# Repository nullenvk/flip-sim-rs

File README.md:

# FLIP

FLIP simulation made in rust. Based on work of Matthias Müller

https://github.com/matthias-research

https://matthias-research.github.io/pages/tenMinutePhysics/index.html

UWAGA: Program należy kompilować z flagą `--release`, w przeciwnym wypadku simulation loop jest dosyć powolny (pełne 60 FPS w release mode vs około 3 FPS w debug mode).

Jak uruchomić:
`cargo run --release`

Parametry symulacji można edytować w `src/main.rs`.

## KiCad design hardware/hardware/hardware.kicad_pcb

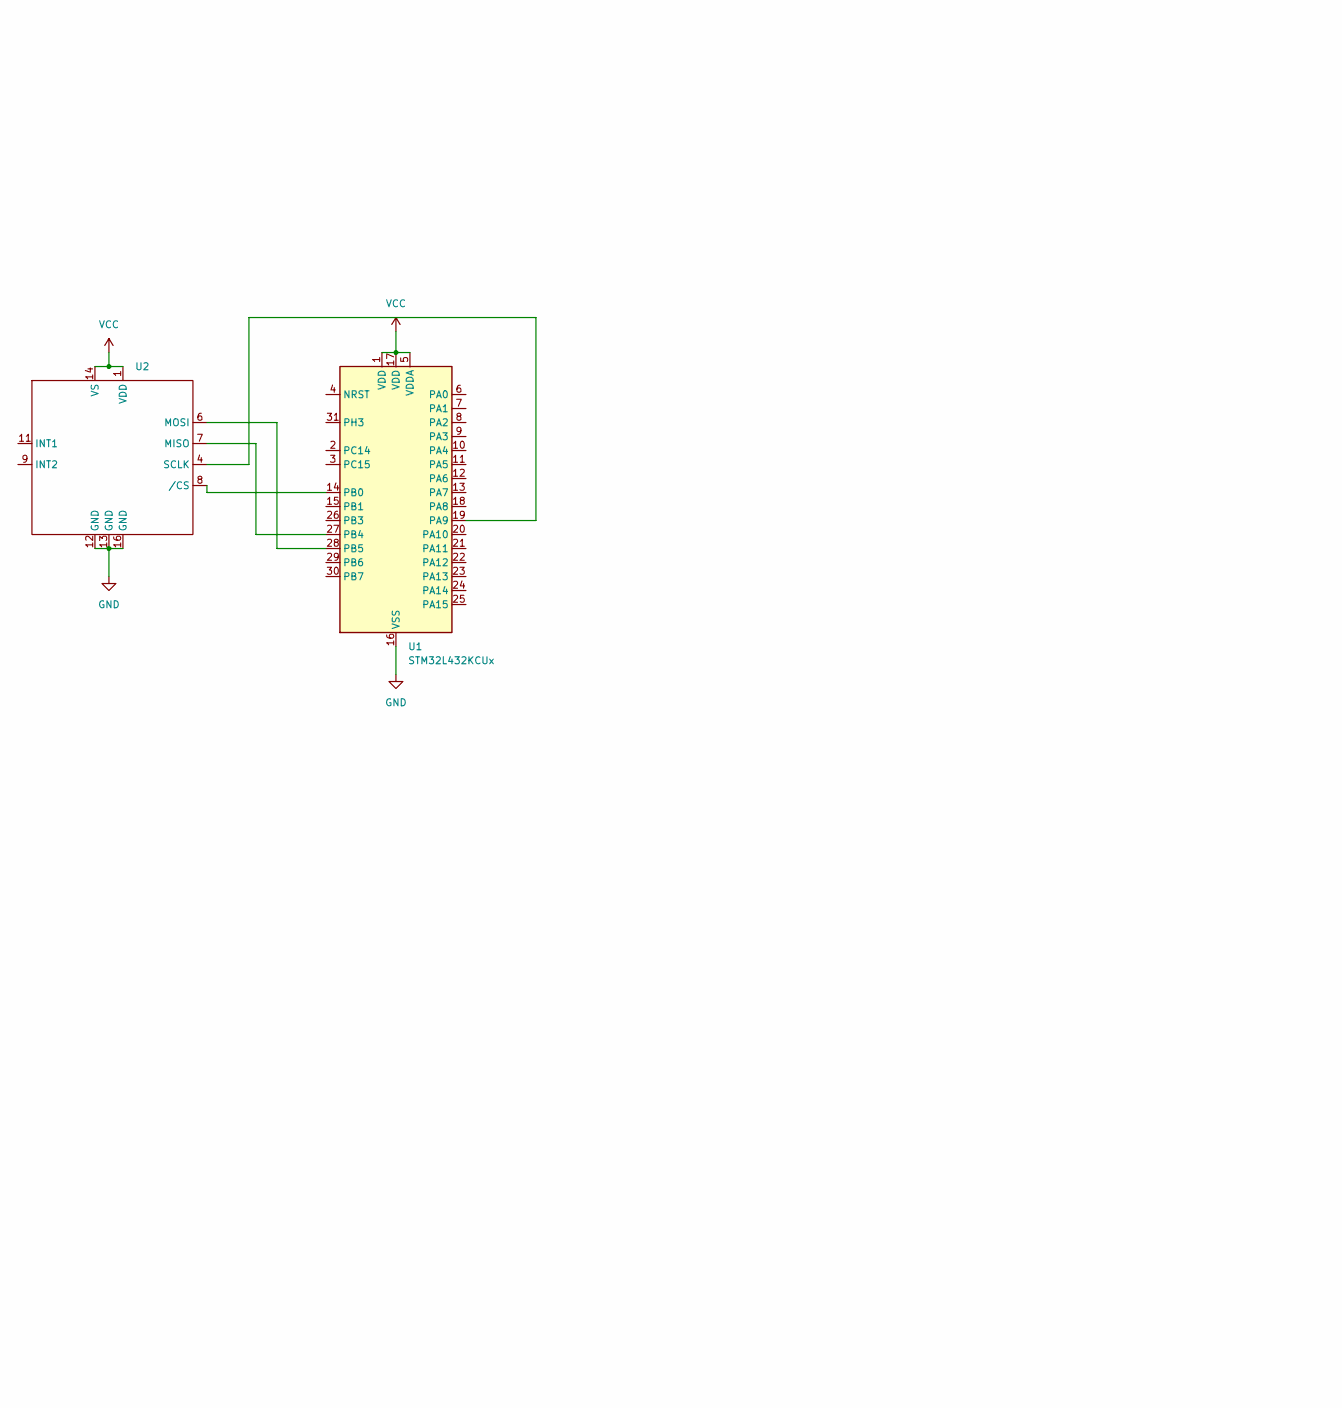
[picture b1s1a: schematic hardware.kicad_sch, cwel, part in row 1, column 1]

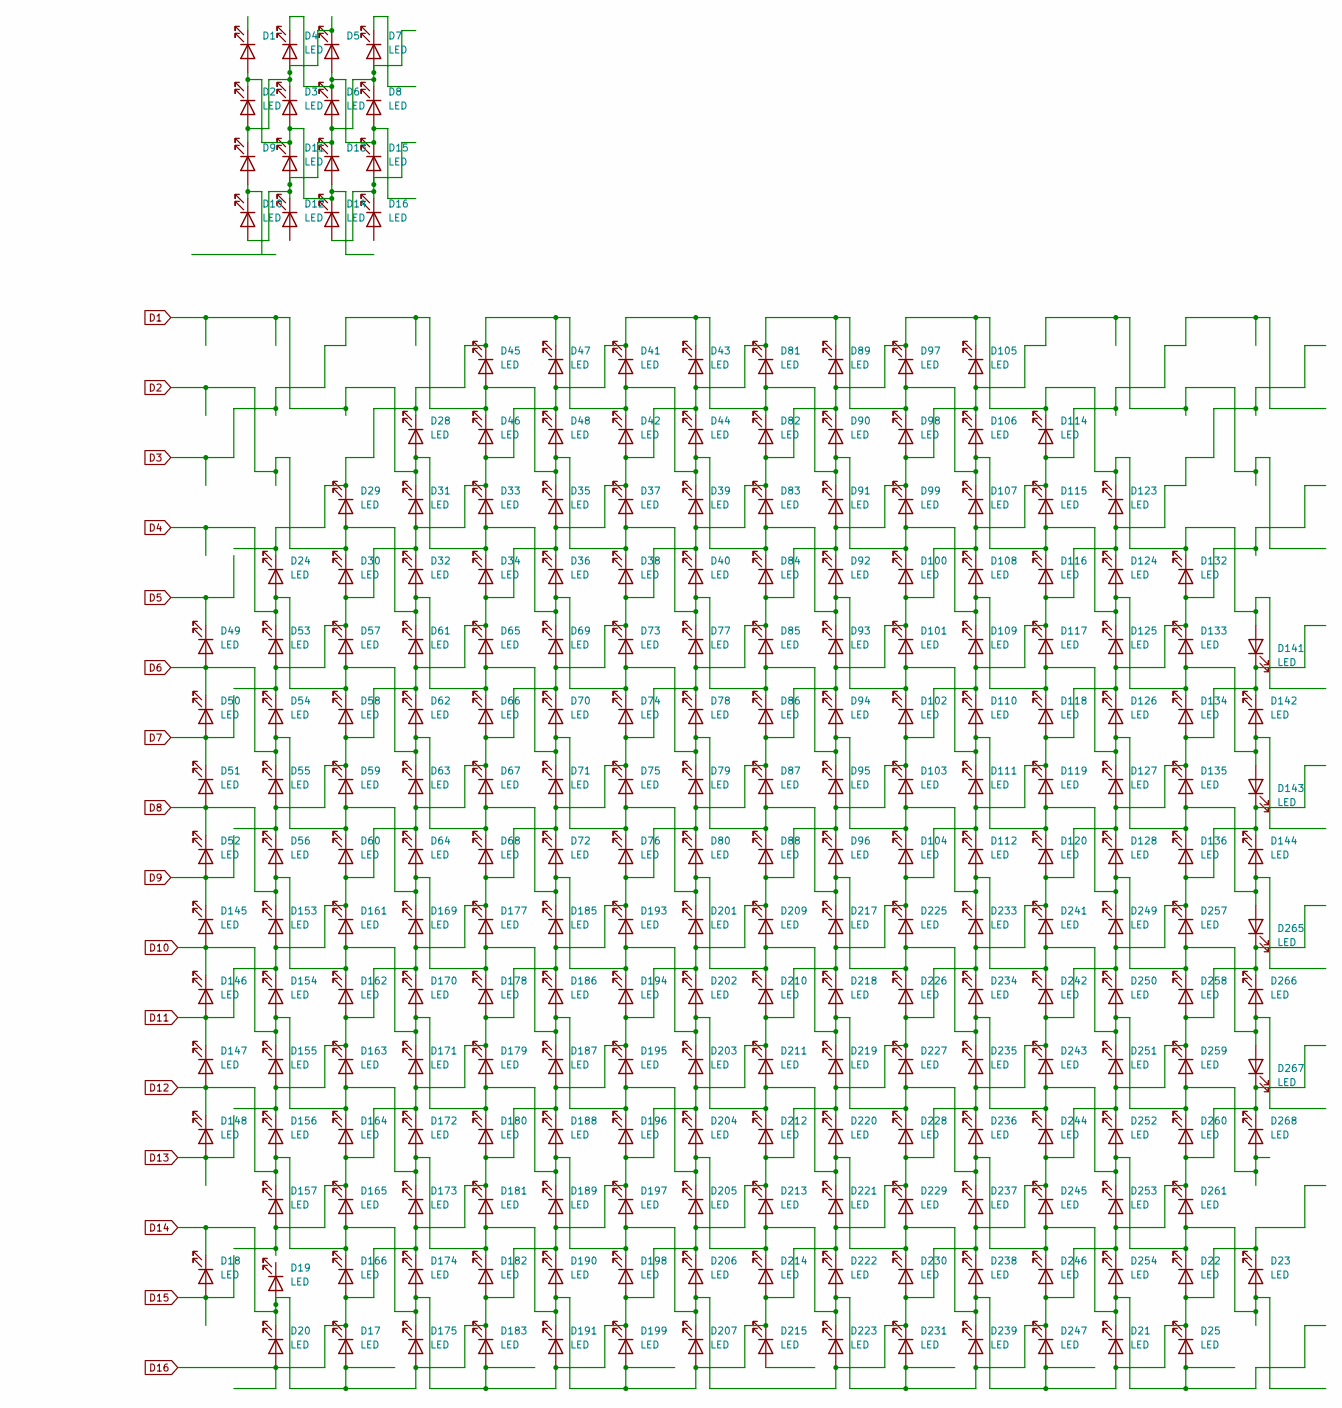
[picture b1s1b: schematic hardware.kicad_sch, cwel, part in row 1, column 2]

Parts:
D1, D2, D3, D4, D5, D6, D7, D8, D9, D10, D11, D12, D13, D14, D15, D16, D17, D18, D19, D20, D21, D22, D23, D24, D25, D28, D29, D30, D31, D32, D33, D34, D35, D36, D37, D38, D39, D40, D41, D42, D43, D44, D45, D46, D47, D48, D49, D50, D51, D52, D53, D54, D55, D56, D57, D58, D59, D60, D61, D62, D63, D64, D65, D66, D67, D68, D69, D70, D71, D72, D73, D74, D75, D76, D77, D78, D79, D80, D81, D82, D83, D84, D85, D86, D87, D88, D89, D90, D91, D92, D93, D94, D95, D96, D97, D98, D99, D100, D101, D102, D103, D104, D105, D106, D107, D108, D109, D110, D111, D112, D114, D115, D116, D117, D118, D119, D120, D123, D124, D125, D126, D127, D128, D132, D133, D134, D135, D136, D141, D142, D143, D144, D145, D146, D147, D148, D153, D154, D155, D156, D157, D161, D162, D163, D164, D165, D166, D169, D170, D171, D172, D173, D174, D175, D177, D178, D179, D180, D181, D182, D183, D185, D186, D187, D188, D189, D190, D191, D193, D194, D195, D196, D197, D198, D199, D201, D202, D203, D204, D205, D206, D207, D209, D210, D211, D212, D213, D214, D215, D217, D218, D219, D220, D221, D222, D223, D225, D226, D227, D228, D229, D230, D231, D233, D234, D235, D236, D237, D238, D239, D241, D242, D243, D244, D245, D246, D247, D249, D250, D251, D252, D253, D254, D257, D258, D259, D260, D261, D265, D266, D267, D268: LED; LED_0402_1005Metric
U1: STM32L432KCUx; QFN-32-1EP_5x5mm_P0.5mm_EP3.45x3.45mm
U2: LGA_CC-16-4_ADI

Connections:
D1: D22.1 (K), D23.2 (A), D28.2 (A), D31.1 (K), D33.2 (A), D34.1 (K), D36.2 (A), D69.1 (K), D73.2 (A), D74.1 (K), D78.2 (A), D79.1 (K), D87.2 (A), D88.1 (K), D96.2 (A), D217.1 (K), D225.2 (A), D226.1 (K), D234.2 (A), D235.1 (K), D243.2 (A), D244.1 (K), D252.2 (A), D253.1 (K), D261.2 (A)
D2: D21.1 (K), D25.2 (A), D29.2 (A), D30.1 (K), D32.2 (A), D61.1 (K), D65.2 (A), D66.1 (K), D70.2 (A), D71.1 (K), D75.2 (A), D76.1 (K), D80.2 (A), D201.1 (K), D209.2 (A), D210.1 (K), D218.2 (A), D219.1 (K), D227.2 (A), D228.1 (K), D236.2 (A), D237.1 (K), D245.2 (A), D246.1 (K), D254.2 (A)
D3: D35.1 (K), D37.2 (A), D38.1 (K), D40.2 (A), D45.2 (A), D46.1 (K), D48.2 (A), D77.1 (K), D85.2 (A), D86.1 (K), D94.2 (A), D95.1 (K), D103.2 (A), D104.1 (K), D112.2 (A), D233.1 (K), D241.2 (A), D242.1 (K), D250.2 (A), D251.1 (K), D259.2 (A), D260.1 (K), D268.2 (A)
D4: D21.2 (A), D22.2 (A), D23.1 (K), D24.2 (A), D25.1 (K), D53.1 (K), D57.2 (A), D58.1 (K), D62.2 (A), D63.1 (K), D67.2 (A), D68.1 (K), D72.2 (A), D185.1 (K), D193.2 (A), D194.1 (K), D202.2 (A), D203.1 (K), D211.2 (A), D212.1 (K), D220.2 (A), D221.1 (K), D229.2 (A), D230.1 (K), D238.2 (A), D239.1 (K), D247.2 (A)
D5: D49.1 (K)
D6: D49.2 (A), D50.1 (K), D54.2 (A), D55.1 (K), D59.2 (A), D60.1 (K), D64.2 (A), D169.1 (K), D177.2 (A), D178.1 (K), D186.2 (A), D187.1 (K), D195.2 (A), D196.1 (K), D204.2 (A), D205.1 (K), D213.2 (A), D214.1 (K), D222.2 (A), D223.1 (K), D231.2 (A), D239.2 (A), D246.2 (A), D247.1 (K), D253.2 (A), D254.1 (K), D260.2 (A), D261.1 (K), D267.1 (K), D268.1 (K)
D7: D50.2 (A), D51.1 (K)
D8: D51.2 (A), D52.1 (K), D56.2 (A), D153.1 (K), D161.2 (A), D162.1 (K), D170.2 (A), D171.1 (K), D179.2 (A), D180.1 (K), D188.2 (A), D189.1 (K), D197.2 (A), D198.1 (K), D206.2 (A), D207.1 (K), D223.2 (A), D230.2 (A), D231.1 (K), D237.2 (A), D238.1 (K), D244.2 (A), D245.1 (K), D251.2 (A), D252.1 (K), D258.2 (A), D259.1 (K), D265.1 (K), D266.1 (K)
D9: D52.2 (A), D145.1 (K)
D10: D136.2 (A), D143.1 (K), D144.1 (K), D145.2 (A), D146.1 (K), D154.2 (A), D155.1 (K), D163.2 (A), D164.1 (K), D172.2 (A), D173.1 (K), D181.2 (A), D182.1 (K), D190.2 (A), D191.1 (K), D199.2 (A), D207.2 (A), D214.2 (A), D215.1 (K_1), D221.2 (A), D222.1 (K), D228.2 (A), D229.1 (K), D235.2 (A), D236.1 (K), D242.2 (A), D243.1 (K), D249.2 (A), D250.1 (K), D257.1 (K)
D11: D38.2 (A), D39.2 (A), D40.1 (K), D60.2 (A), D63.2 (A), D64.1 (K), D66.2 (A), D67.1 (K), D69.2 (A), D70.1 (K), D73.1 (K), D82.2 (A), D83.1 (K), D89.2 (A), D90.1 (K), D97.1 (K), D105.1 (K), D114.1 (K), D123.1 (K), D132.1 (K), D141.2 (A), D146.2 (A), D147.1 (K), D153.2 (A), D154.1 (K), D161.1 (K)
D12: D120.2 (A), D127.2 (A), D128.1 (K), D134.2 (A), D135.1 (K), D141.1 (K), D142.1 (K), D147.2 (A), D148.1 (K), D156.2 (A), D157.1 (K), D165.2 (A), D166.1 (K), D174.2 (A), D175.1 (K), D183.2 (A), D191.2 (A), D198.2 (A), D199.1 (K), D205.2 (A), D206.1 (K), D212.2 (A), D213.1 (K), D219.2 (A), D220.1 (K), D226.2 (A), D227.1 (K), D233.2 (A), D234.1 (K), D241.1 (K)
D13: D148.2 (A)
D14: D17.2 (A), D18.1 (K), D19.2 (A_2), D20.1 (K), D104.2 (A), D111.2 (A), D112.1 (K), D118.2 (A), D119.1 (K), D125.2 (A), D126.1 (K), D132.2 (A), D133.1 (K), D175.2 (A), D182.2 (A), D183.1 (K), D189.2 (A), D190.1 (K), D196.2 (A), D197.1 (K), D203.2 (A), D204.1 (K), D210.2 (A), D211.1 (K), D217.2 (A), D218.1 (K), D225.1 (K)
D15: D18.2 (A)
D16: D17.1 (K), D20.2 (A), D88.2 (A), D95.2 (A), D96.1 (K), D102.2 (A), D103.1 (K), D109.2 (A), D110.1 (K), D116.2 (A), D117.1 (K), D123.2 (A), D124.1 (K), D166.2 (A), D173.2 (A), D174.1 (K), D180.2 (A), D181.1 (K), D187.2 (A), D188.1 (K), D194.2 (A), D195.1 (K), D201.2 (A), D202.1 (K), D209.1 (K)
GND: U1.16 (VSS), U1.32 (VSS), U1.33 (VSS), U2.12 (GND), U2.13 (GND), U2.16 (GND)
unnamed: D1.2 (A_2), D2.1 (K), D3.2 (A), D11.1 (K), D13.2 (A), D14.1 (K)
unnamed: D2.2 (A), D3.1 (K), D4.2 (A), D5.1 (K), D9.1 (K)
unnamed: D6.2 (A), D7.2 (A_2), D8.1 (K), D10.2 (A), D11.2 (A), D12.1 (K_1), D13.1 (K)
unnamed: D9.2 (A), D10.1 (K)
unnamed: D14.2 (A), D15.2 (A), D16.1 (K_1)
unnamed: D4.1 (K), D5.2 (A), D6.1 (K), D8.2 (A), D15.1 (K)
unnamed: D76.2 (A), D79.2 (A), D80.1 (K), D86.2 (A), D87.1 (K), D93.2 (A), D94.1 (K), D100.2 (A), D101.1 (K), D107.2 (A), D108.1 (K), D114.2 (A), D115.1 (K), D157.2 (A), D164.2 (A), D165.1 (K), D171.2 (A), D172.1 (K), D178.2 (A), D179.1 (K), D185.2 (A), D186.1 (K), D193.1 (K)
unnamed: D30.2 (A), D31.2 (A), D32.1 (K), D33.1 (K), D41.1 (K), D43.1 (K), D46.2 (A), D47.2 (A), D48.1 (K), D53.2 (A), D54.1 (K), D57.1 (K), D81.2 (A), D82.1 (K), D90.2 (A), D91.1 (K), D99.2 (A), D100.1 (K), D108.2 (A), D109.1 (K), D117.2 (A), D118.1 (K), D126.2 (A), D127.1 (K), D135.2 (A), D136.1 (K), D144.2 (A), D265.2 (A)
unnamed: D24.1 (K), D28.1 (K), D29.1 (K), D39.1 (K), D41.2 (A), D42.1 (K), D44.2 (A), D45.1 (K), D47.1 (K), D83.2 (A), D84.1 (K), D92.2 (A), D93.1 (K), D101.2 (A), D102.1 (K), D110.2 (A), D111.1 (K), D119.2 (A), D120.1 (K), D128.2 (A), D249.1 (K), D257.2 (A), D258.1 (K), D266.2 (A), D267.2 (A)
unnamed: D68.2 (A), D71.2 (A), D72.1 (K), D74.2 (A), D75.1 (K), D77.2 (A), D78.1 (K), D84.2 (A), D85.1 (K), D91.2 (A), D92.1 (K), D98.2 (A), D99.1 (K), D105.2 (A), D106.1 (K), D155.2 (A), D156.1 (K), D162.2 (A), D163.1 (K), D169.2 (A), D170.1 (K), D177.1 (K)
unnamed: D34.2 (A), D35.2 (A), D36.1 (K), D37.1 (K), D42.2 (A), D43.2 (A), D44.1 (K), D55.2 (A), D56.1 (K), D58.2 (A), D59.1 (K), D61.2 (A), D62.1 (K), D65.1 (K), D81.1 (K), D89.1 (K), D97.2 (A), D98.1 (K), D106.2 (A), D107.1 (K), D115.2 (A), D116.1 (K), D124.2 (A), D125.1 (K), D133.2 (A), D134.1 (K), D142.2 (A), D143.2 (A)
unnamed: U1.19 (PA9), U2.4 (SCLK)
unnamed: U1.14 (PB0), U2.8 (/CS)
unnamed: U1.27 (PB4), U2.7 (MISO)
unnamed: U1.28 (PB5), U2.6 (MOSI)
VCC: U1.1 (VDD), U1.5 (VDDA), U1.17 (VDD), U2.1 (VDD), U2.14 (VS)

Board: 2 copper layers, 234 parts (0 on the bottom side), 30 nets, no tracks yet.

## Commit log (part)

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2026-05-21 initial structure
2026-05-21 Example of how UI should work
2026-05-23 config update
2026-05-23 i am very stupid but it now works maybe
2026-05-23 sim constructor updates
2026-05-23 Doesn't work, no idea why, most of this code should be rewritten
2026-05-23 wgpu code based on the official tutorial
2026-05-23 wroking wgpu
2026-05-23 clanker fixes
2026-05-24 overrelaxation set to 1.0 and it somehow works :3
2026-05-24 tank boundaries shenanigans, nothing much tbh
2026-05-24 grid drawing
2026-05-24 grid drawing fixed
2026-05-24 final?
2026-05-25 Implement terrible collision detection
2026-05-25 mouse gravity
2026-05-25 chat cooked with that
2026-05-25 chat cooked again with the handle collisions :3
2026-05-25 Prevent balls from entering walls
2026-05-25 Performance
2026-05-25 fluid now can't get stuck on circle border
2026-05-26 collision cooking pt2
2026-05-29 Embassy switch
2026-05-29 Cargo internal files
2026-05-29 copied sim from other branch
2026-05-30 i would rather stick my cock in dishwaser instead of doind this shitty shit
2026-05-30 Fix floats
2026-05-30 meow
2026-05-30 szpont działa
2026-05-30 Change scaling
2026-05-30 config changes
2026-06-17 handle particle collsiosn fix
2026-06-17 remove a comment
2026-06-17 Add egui
2026-06-17 refactor wgpu
2026-06-17 egui
2026-06-17 egui scaling
